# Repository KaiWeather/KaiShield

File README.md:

# KaiShield
Arduino Shield with capabilities of being a independent entity with a XBee.

PCB files for KaiShield for Arduino

Format is EagleCAD schematic and board layout

Designed by Kai Weather.  
Creative Commons Attribution, Share-Alike license, check license.txt for more information
All text above must be included in any redistribution

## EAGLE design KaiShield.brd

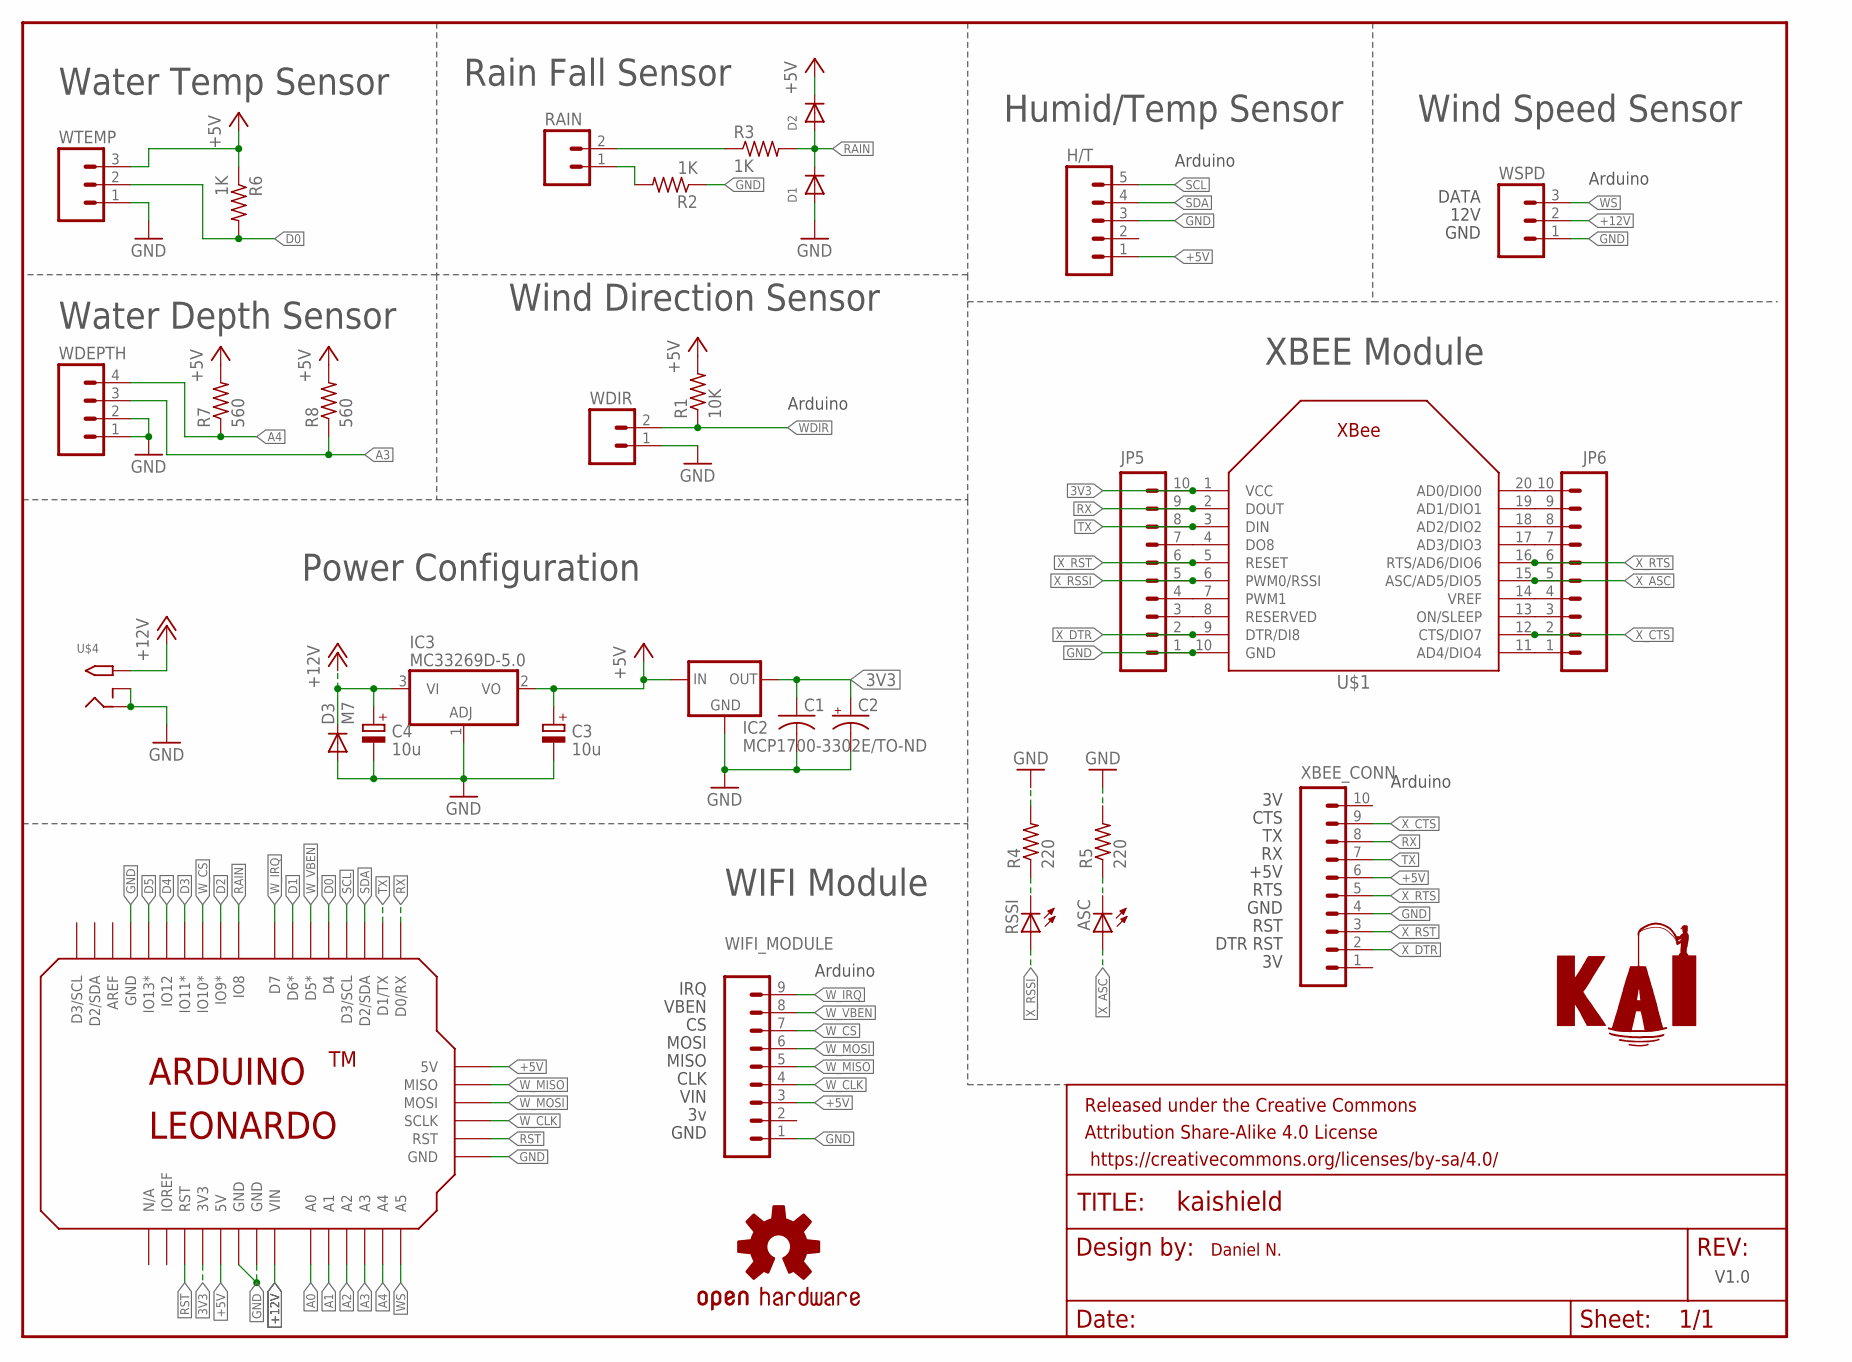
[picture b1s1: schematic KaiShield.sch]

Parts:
ASC: LED3MM
C1: C-US025-025X050; C025-025X050
C2: CPOL-USE2.5-5; E2,5-5
C3, C4: 10u; SMC_B
D1, D2: DIODEDO-1N4148; DO-1N4148
D3: M7; SMB
FRAME1: FRAME-LETTERNO_PACKAGE; DUMMY
H/T: M05PTH; 1X05
IC2: MCP1700-3302E/TO-ND; TO92
IC3: MC33269D-5.0; DPACK
JP5, JP6: M10SILK_FEMALE_PTH; 1X10
LOGO1: OSHW-LOGOM; OSHW-LOGO-M
R1: 10K; 0207/10
R2, R3, R6: 1K; 0207/10
R4, R5: 220; 0207/10
R7, R8: 560; 0207/10
RAIN: M02PTH; 1X02
RSSI: LED3MM
U$1: XBEE
U$2: LEONARDO
U$3: KAI_LOGO
U$4: 2.1MMJACKTHM; PJ-102A
WDEPTH: M04PTH; 1X04
WDIR: M02PTH; 1X02
WIFI_MODULE: M09; 1X09
WSPD: M03PTH; 1X03
WTEMP: M03PTH; 1X03
XBEE_CONN: M10SILK_FEMALE_PTH; 1X10

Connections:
3V3: C1.1, C2.+, IC2.3 (OUT), JP5.10, U$1.1 (VCC), U$2.3V (3V3)
+5V: C3.+, D2.C, H/T.1, IC2.2 (IN), IC3.2 (VO), R1.2, R6.1, R7.2, R8.2, U$2.5V, U$2.5V@1 (5V), WIFI_MODULE.3, WTEMP.3, XBEE_CONN.6
+12V: C4.+, D3.C, IC3.3 (VI), U$2.VIN, U$4.TIP, WSPD.2
A0: U$2.A0
A1: U$2.A1
A2: U$2.A2
A3: R8.1, U$2.A3, WDEPTH.3
A4: R7.1, U$2.A4, WDEPTH.4
D0: R6.2, U$2.D4, WTEMP.2
D1: U$2.D6 (D6*)
D2: U$2.D9 (IO9*)
D3: U$2.D11 (IO11*)
D4: U$2.D12 (IO12)
D5: U$2.D13 (IO13*)
GND: C1.2, C2.-, C3.-, C4.-, D1.A, D3.A, H/T.3, IC2.1 (GND), IC3.1 (ADJ), JP5.1, R2.1, R4.2, R5.2, U$1.10 (GND), U$2.GND, U$2.GND1 (GND), U$2.GND2 (GND), U$2.GND3 (GND), U$4.RING, U$4.RING_SW, WDEPTH.1, WDEPTH.2, WDIR.1, WIFI_MODULE.1, WSPD.1, WTEMP.1, XBEE_CONN.4
unnamed: R3.1, RAIN.2
unnamed: JP6.4, U$1.14 (VREF)
unnamed: R2.2, RAIN.1
unnamed: JP6.3, U$1.13 (ON/SLEEP)
unnamed: R4.1, RSSI.K (C)
unnamed: ASC.K (C), R5.1
unnamed: JP5.7, U$1.4 (DO8)
unnamed: JP5.4, U$1.7 (PWM1)
unnamed: JP5.3, U$1.8 (RESERVED)
RAIN: D1.C, D2.A, R3.2, U$2.D8 (IO8)
RST: U$2.RST, U$2.RST. (RST)
RX: JP5.9, U$1.2 (DOUT), U$2.D0 (D0/RX), XBEE_CONN.8
SCL: H/T.5, U$2.D3SCL (D3/SCL)
SDA: H/T.4, U$2.D2SDA (D2/SDA)
TX: JP5.8, U$1.3 (DIN), U$2.D1 (D1/TX), XBEE_CONN.7
WDIR: R1.1, WDIR.2
WS: U$2.A5, WSPD.3
W_CLK: U$2.SCLK, WIFI_MODULE.4
W_CS: U$2.D10 (IO10*), WIFI_MODULE.7
W_IRQ: U$2.D7, WIFI_MODULE.9
W_MISO: U$2.MISO, WIFI_MODULE.5
W_MOSI: U$2.MOSI, WIFI_MODULE.6
W_VBEN: U$2.D5 (D5*), WIFI_MODULE.8
X0: JP6.10, U$1.20 (AD0/DIO0)
X1: JP6.9, U$1.19 (AD1/DIO1)
X2: JP6.8, U$1.18 (AD2/DIO2)
X3: JP6.7, U$1.17 (AD3/DIO3)
X4: JP6.1, U$1.11 (AD4/DIO4)
X_ASC: ASC.A, JP6.5, U$1.15 (ASC/AD5/DIO5)
X_CTS: JP6.2, U$1.12 (CTS/DIO7), XBEE_CONN.9
X_DTR: JP5.2, U$1.9 (DTR/DI8), XBEE_CONN.2
X_RSSI: JP5.5, RSSI.A, U$1.6 (PWM0/RSSI)
X_RST: JP5.6, U$1.5 (RESET), XBEE_CONN.3
X_RTS: JP6.6, U$1.16 (RTS/AD6/DIO6), XBEE_CONN.5

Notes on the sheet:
Daniel N.
V1.0
XBEE Module
WIFI Module
RTS
+5V
CTS
GND
RST
DTR RST
VIN
CLK
MISO
MOSI
VBEN
IRQ
Humid/Temp Sensor
Wind Speed Sensor
12V
DATA
Rain Fall Sensor
Wind Direction Sensor
Arduino
Power Configuration
Water Temp Sensor
Water Depth Sensor

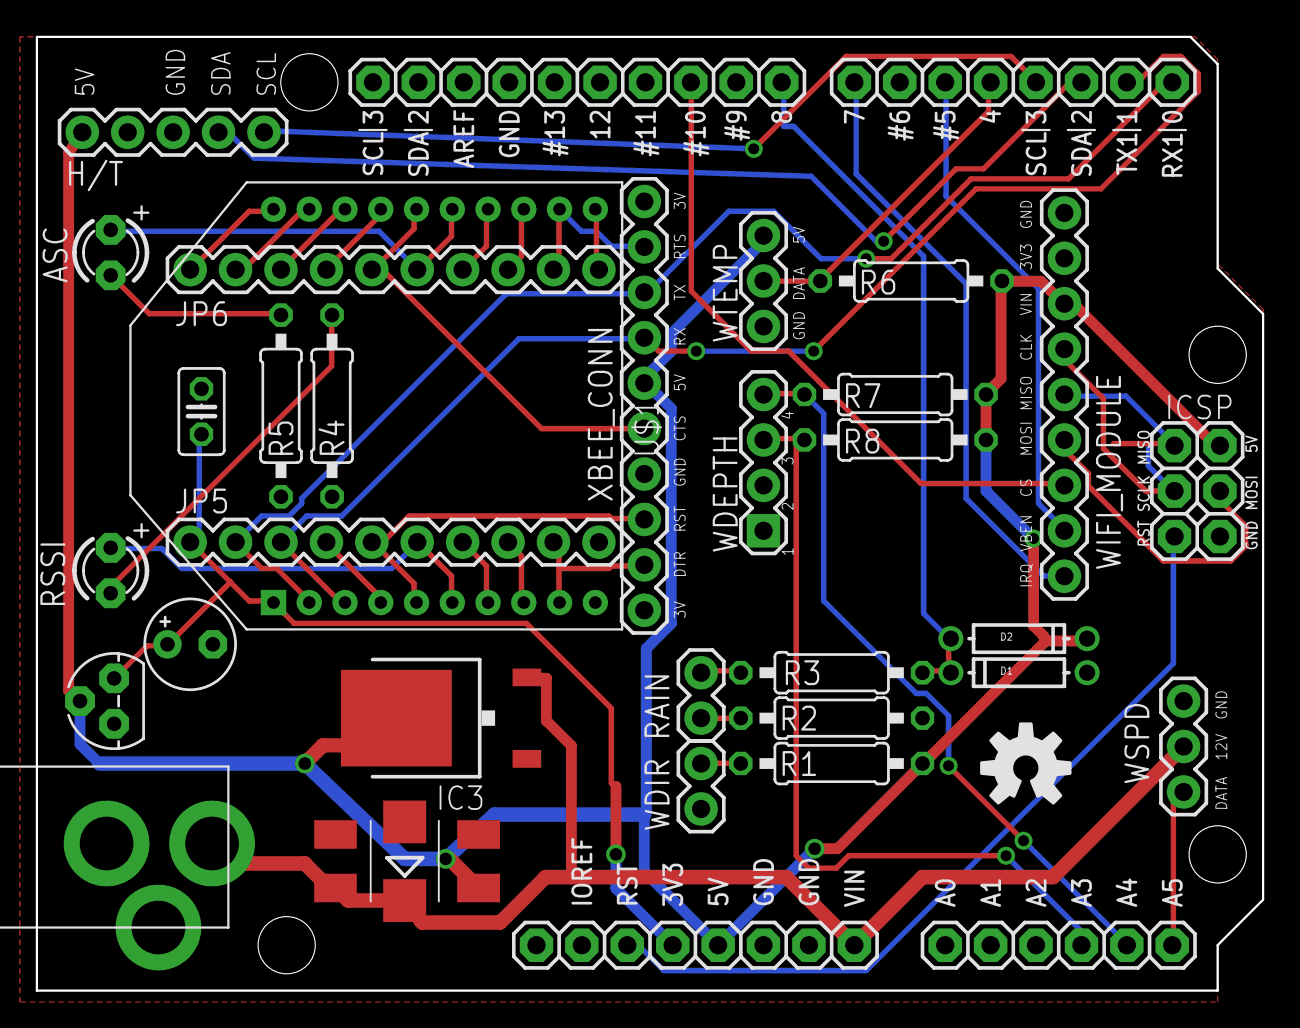
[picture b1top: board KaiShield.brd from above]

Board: 2 copper layers, 68.6 x 53.3 mm, 35 parts (1 on the bottom side), 41 nets.

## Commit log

2015-04-06 Added KaiShield Version 1.0
2015-04-06 Updated KaiShield board and added two more sensors. Now this is the main board instead of just a station board :D.
2015-04-06 updated KaiShield with the new power ic foot print DPAK

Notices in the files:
parts and their libraries:
SparkFun-Connectors: Licensing: Creative Commons ShareAlike 4.0 International - https://creativecommons.org/licenses/by-sa/4.0
SparkFun-Aesthetics: Released under the Creative Commons Attribution Share-Alike 4.0 License
SparkFun-Aesthetics: https://creativecommons.org/licenses/by-sa/4.0
